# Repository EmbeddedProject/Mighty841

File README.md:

# Mighty841
Yet another Attiny841 dev board in order to learn Kicad

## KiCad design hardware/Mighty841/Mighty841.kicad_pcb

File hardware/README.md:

# Hardware folder organization:
-----------------------------

 - 3d_models &nbsp;&nbsp;&nbsp; _// .STEP and .WRL model files for all footprints_
 - datasheets &nbsp;&nbsp;&nbsp; _// data sheets for components used_
 - gerber &nbsp;&nbsp;&nbsp; _// final production files_
 - images &nbsp;&nbsp;&nbsp; _// SVG images and 3D board renders_
 - lib_sch &nbsp;&nbsp;&nbsp; _// schematic symbols_
 - lib_fp.pretty &nbsp;&nbsp;&nbsp; _// footprints_
 - pdf &nbsp;&nbsp;&nbsp;&nbsp;&nbsp; _// schematics, board layouts, dimension drawings_

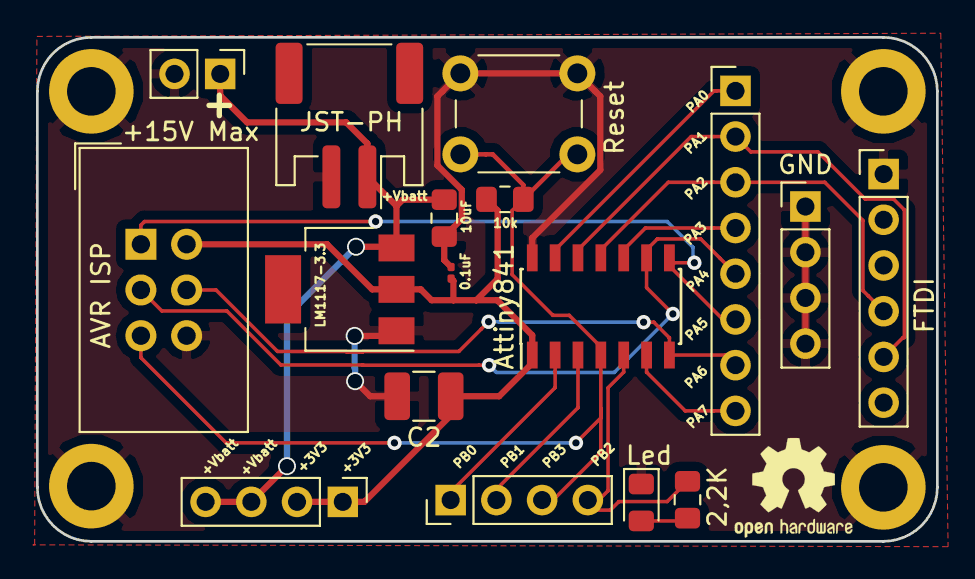
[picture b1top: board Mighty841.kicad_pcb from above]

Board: 2 copper layers, 50.0 x 28.0 mm, 21 parts (0 on the bottom side), 16 nets.

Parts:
0.1uF: 0.1µF; C_0201_0603Metric
2,2K: 2.2k; R_0805_2012Metric_Pad1.15x1.40mm_HandSolder
10k: 10k; R_0805_2012Metric_Pad1.15x1.40mm_HandSolder
10uF: 10µF; C_0805_2012Metric_Pad1.15x1.40mm_HandSolder
+15V Max: Power Supply; PinHeader_1x02_P2.54mm_Vertical
AVR ISP: AVR-ISP-6; IDC-Header_2x03_P2.54mm_Vertical
Attiny841: ATtiny841-SSU; SOIC-14_3.9x8.7mm_P1.27mm
C2: 100µF; C_1210_3225Metric_Pad1.42x2.65mm_HandSolder
FTDI: FDTI; PinHeader_1x06_P2.54mm_Vertical
GND: GND; PinHeader_1x04_P2.54mm_Vertical
GND#2: Port A; PinHeader_1x08_P2.54mm_Vertical
H1, H2, H3, H4: MountingHole_Pad; MountingHole_2.7mm_M2.5_DIN965_Pad
J5: Port B; PinHeader_1x04_P2.54mm_Vertical
J6: 3,3V - VBatt; PinHeader_1x04_P2.54mm_Vertical
JST-PH: JST-PH-2.0mm; JST_PH_S2B-PH-SM4-TB_1x02-1MP_P2.00mm_Horizontal
LM1117-3.3: LM1117-3.3; SOT-223
Led : User LED; LED_0805_2012Metric_Pad1.15x1.40mm_HandSolder
Reset: SW_Push_Dual; SW_PUSH_6mm

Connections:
+3V3: 0.1uF.1, 10k.2, AVR ISP.2, Attiny841.1, C2.1, J6.1, J6.2, LM1117-3.3.2
+BATT: 10uF.1, +15V Max.1, J6.3, J6.4, JST-PH.1, LM1117-3.3.3
GND: 0.1uF.2, 10uF.2, +15V Max.2, AVR ISP.6, Attiny841.14, C2.2, FTDI.1, GND.1, GND.2, GND.3, GND.4, H1.1, H2.1, H3.1, H4.1, JST-PH.2, LM1117-3.3.1, Led.1, Reset.1
unnamed: 2,2K.2, Led.2
PA0: Attiny841.13, GND#2.1
PA1: Attiny841.12, FTDI.5, GND#2.2
PA2: Attiny841.11, FTDI.4, GND#2.3
PA3: Attiny841.10, GND#2.4
PA4: AVR ISP.3, Attiny841.9, GND#2.5
PA5: AVR ISP.1, Attiny841.8, GND#2.6
PA6: AVR ISP.4, Attiny841.7, GND#2.7
PA7: Attiny841.6, GND#2.8
PB0: Attiny841.2, J5.1
PB1: Attiny841.3, J5.2
PB2: 2,2K.1, Attiny841.5, J5.4
PB3: 10k.1, AVR ISP.5, Attiny841.4, J5.3, Reset.2

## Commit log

2019-01-15 add README
2019-01-15 add hardware folder structure and datasheet
2019-01-15 hw: change syntax readme.md
2019-01-23 HW: first release PCB
